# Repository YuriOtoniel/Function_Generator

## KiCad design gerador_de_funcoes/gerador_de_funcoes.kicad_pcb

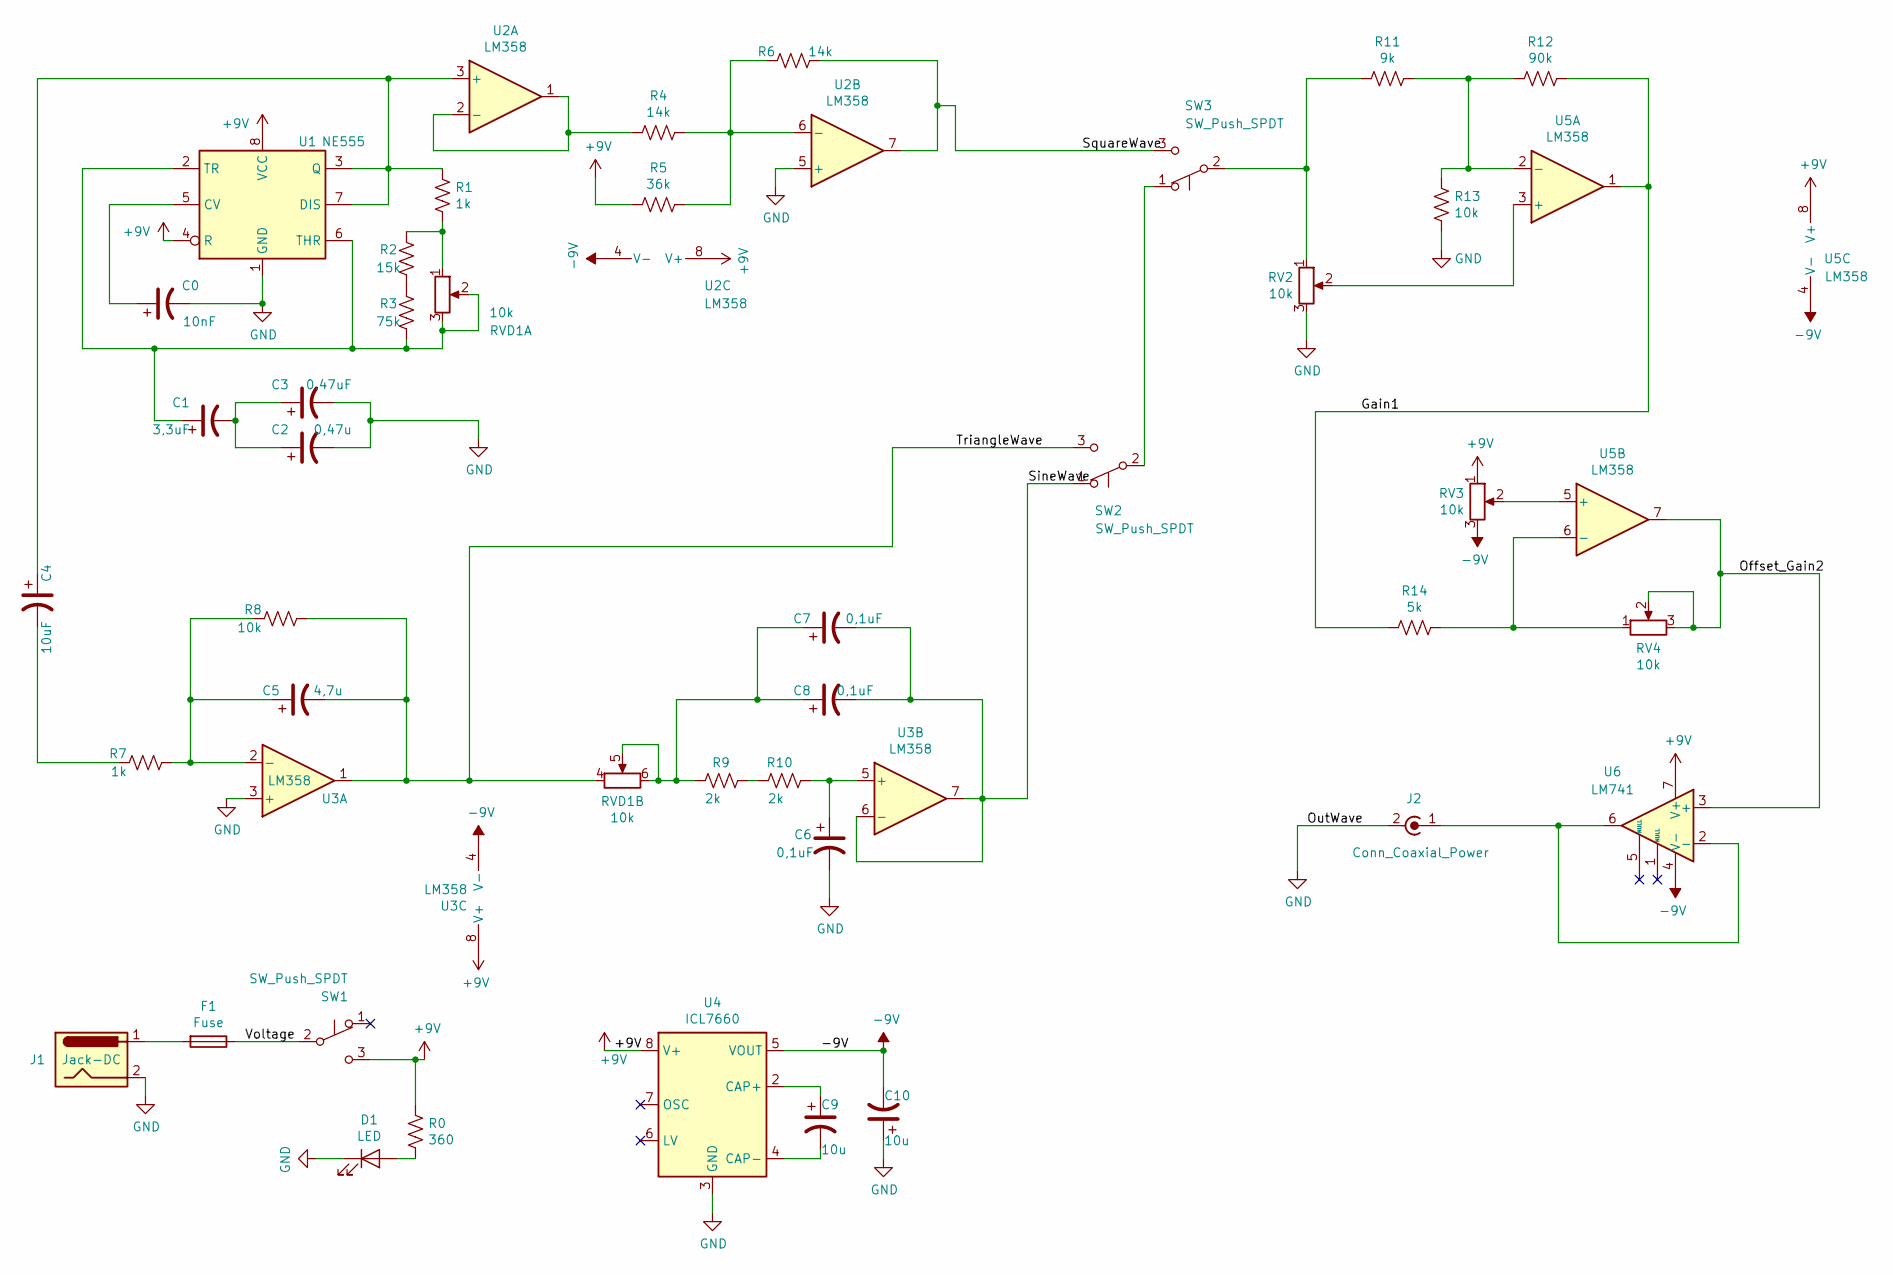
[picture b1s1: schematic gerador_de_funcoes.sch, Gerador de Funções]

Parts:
C0: 10nF; CP_Radial_D6.3mm_P2.50mm
C1: 3,3uF; CP_Radial_D6.3mm_P2.50mm
C2: 0,47u; CP_Radial_D6.3mm_P2.50mm
C3: 0,47uF; CP_Radial_D6.3mm_P2.50mm
C4: 10uF; CP_Radial_D6.3mm_P2.50mm
C5: 4,7u; CP_Radial_D6.3mm_P2.50mm
C6, C7, C8: 0,1uF; CP_Radial_D6.3mm_P2.50mm
C9, C10: 10u; CP_Radial_D6.3mm_P2.50mm
D1: LED; LED_D3.0mm
F1: Fuse; Fuseholder_Cylinder-5x20mm_Schurter_0031_8201_Horizontal_Op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
J1: Jack-DC; BarrelJack_Horizontal
J2: Conn_Coaxial_Power; BNC_Amphenol_B6252HB-NPP3G-50_Horizontal
R0: 360; R_Axial_DIN0204_L3.6mm_D1.6mm_P5.08mm_Horizontal
R1, R7: 1k; R_Axial_DIN0204_L3.6mm_D1.6mm_P5.08mm_Horizontal
R2: 15k; R_Axial_DIN0204_L3.6mm_D1.6mm_P5.08mm_Horizontal
R3: 75k; R_Axial_DIN0204_L3.6mm_D1.6mm_P5.08mm_Horizontal
R4, R6: 14k; R_Axial_DIN0204_L3.6mm_D1.6mm_P5.08mm_Horizontal
R5: 36k; R_Axial_DIN0204_L3.6mm_D1.6mm_P5.08mm_Horizontal
R8, R13: 10k; R_Axial_DIN0204_L3.6mm_D1.6mm_P5.08mm_Horizontal
R9, R10: 2k; R_Axial_DIN0204_L3.6mm_D1.6mm_P5.08mm_Horizontal
R11: 9k; R_Axial_DIN0204_L3.6mm_D1.6mm_P5.08mm_Horizontal
R12: 90k; R_Axial_DIN0204_L3.6mm_D1.6mm_P5.08mm_Horizontal
R14: 5k; R_Axial_DIN0204_L3.6mm_D1.6mm_P5.08mm_Horizontal
RV2, RV3, RV4: 10k; Potentiometer_Alps_RK163_Single_Horizontal
RVD1: 10k; Potentiometer_Alps_RK163_Dual_Horizontal
SW1, SW2, SW3: SW_Push_SPDT; SW_E-Switch_EG1224_SPDT_Angled
U1: NE555; DIP-8_W7.62mm
U2, U3: LM358; DIP-8_W7.62mm_LongPads
U4: ICL7660; DIP-8_W7.62mm_LongPads
U5: LM358; DIP-8_W7.62mm
U6: LM741; DIP-8_W7.62mm_LongPads

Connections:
+9V: R0.1, R5.1, RV3.1, SW1.3 (C), U1.4 (R), U1.8 (VCC), U2.8 (V+), U3.8 (V+), U4.8 (V+), U5.8 (V+), U6.7 (V+)
-9V: C10.2, RV3.3, U2.4 (V-), U3.4 (V-), U4.5 (VOUT), U5.4 (V-), U6.4 (V-)
/Gain1: R12.1, R14.2, U5.1
/Offset_Gain2: RV4.2, RV4.3, U5.7, U6.3 (+)
/SineWave: C7.2, C8.2, SW2.1 (A), U3.6 (-), U3.7
/SquareWave: R6.2, SW3.3 (C), U2.7
/TriangleWave: C5.2, R8.2, RVD1.4, SW2.3 (C), U3.1
/Voltage: F1.1, SW1.2 (B)
GND: C0.2, C2.2, C3.2, C6.2, C10.1, D1.1 (K), J1.2, J2.2 (Ext), R13.2, RV2.3, U1.1 (GND), U2.5 (+), U3.3 (+), U4.3 (GND)
unnamed: C0.1, U1.5 (CV)
unnamed: C1.1, R3.1, RVD1.2, RVD1.3, U1.2 (TR), U1.6 (THR)
unnamed: C1.2, C2.1, C3.1
unnamed: C4.1, R1.1, U1.3 (Q), U1.7 (DIS), U2.3 (+)
unnamed: C4.2, R7.1
unnamed: C5.1, R7.2, R8.1, U3.2 (-)
unnamed: C6.1, R10.2, U3.5 (+)
unnamed: C7.1, C8.1, R9.1, RVD1.5, RVD1.6
unnamed: C9.1, U4.2 (CAP+)
unnamed: C9.2, U4.4 (CAP-)
unnamed: D1.2 (A), R0.2
unnamed: F1.2, J1.1
unnamed: J2.1 (In), U6.2 (-), U6.6
unnamed: R1.2, R2.2, RVD1.1
unnamed: R2.1, R3.2
unnamed: R4.1, U2.1, U2.2 (-)
unnamed: R4.2, R5.2, R6.1, U2.6 (-)
unnamed: R9.2, R10.1
unnamed: R11.1, R12.2, R13.1, U5.2 (-)
unnamed: R11.2, RV2.1, SW3.2 (B)
unnamed: R14.1, RV4.1, U5.6 (-)
unnamed: RV2.2, U5.3 (+)
unnamed: RV3.2, U5.5 (+)
unnamed: SW2.2 (B), SW3.1 (A)

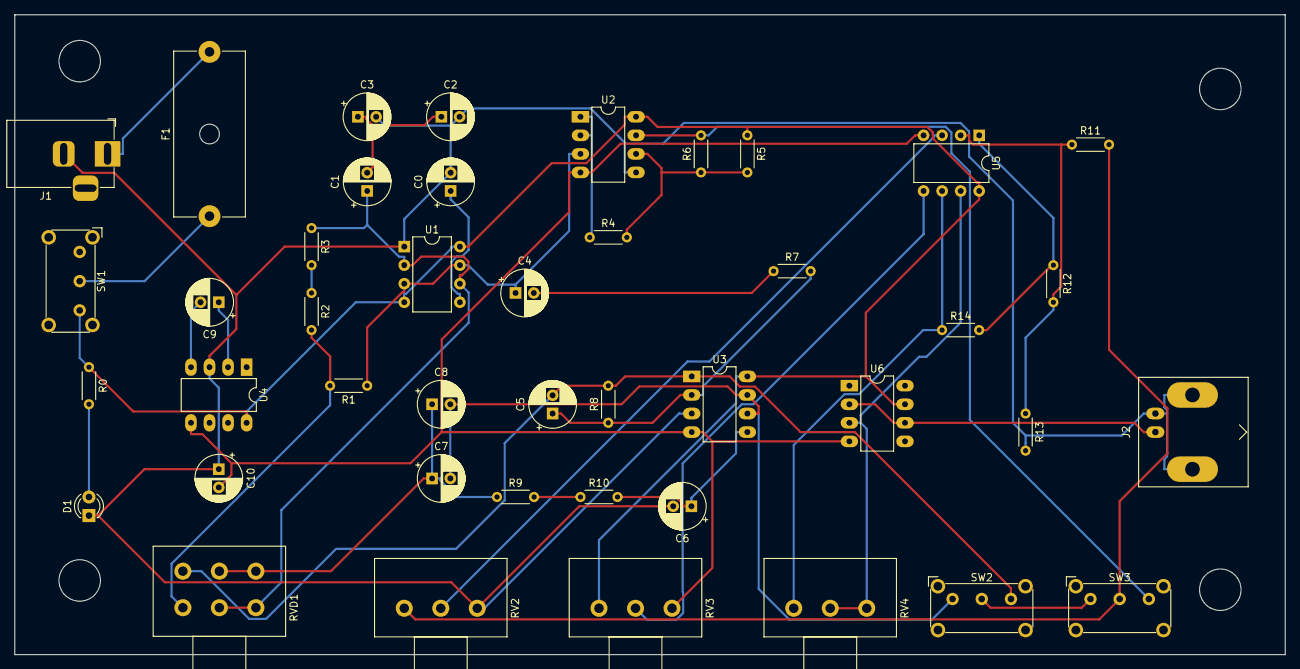
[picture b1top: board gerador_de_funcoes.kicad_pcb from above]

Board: 2 copper layers, 174.0 x 87.6 mm, 43 parts (0 on the bottom side), 33 nets.
